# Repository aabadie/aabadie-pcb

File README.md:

aabadie-pcb board design and support
====================================

This repository contains both the Kicad project used to design aabadie-pcb board and also a RIOT port to this board.

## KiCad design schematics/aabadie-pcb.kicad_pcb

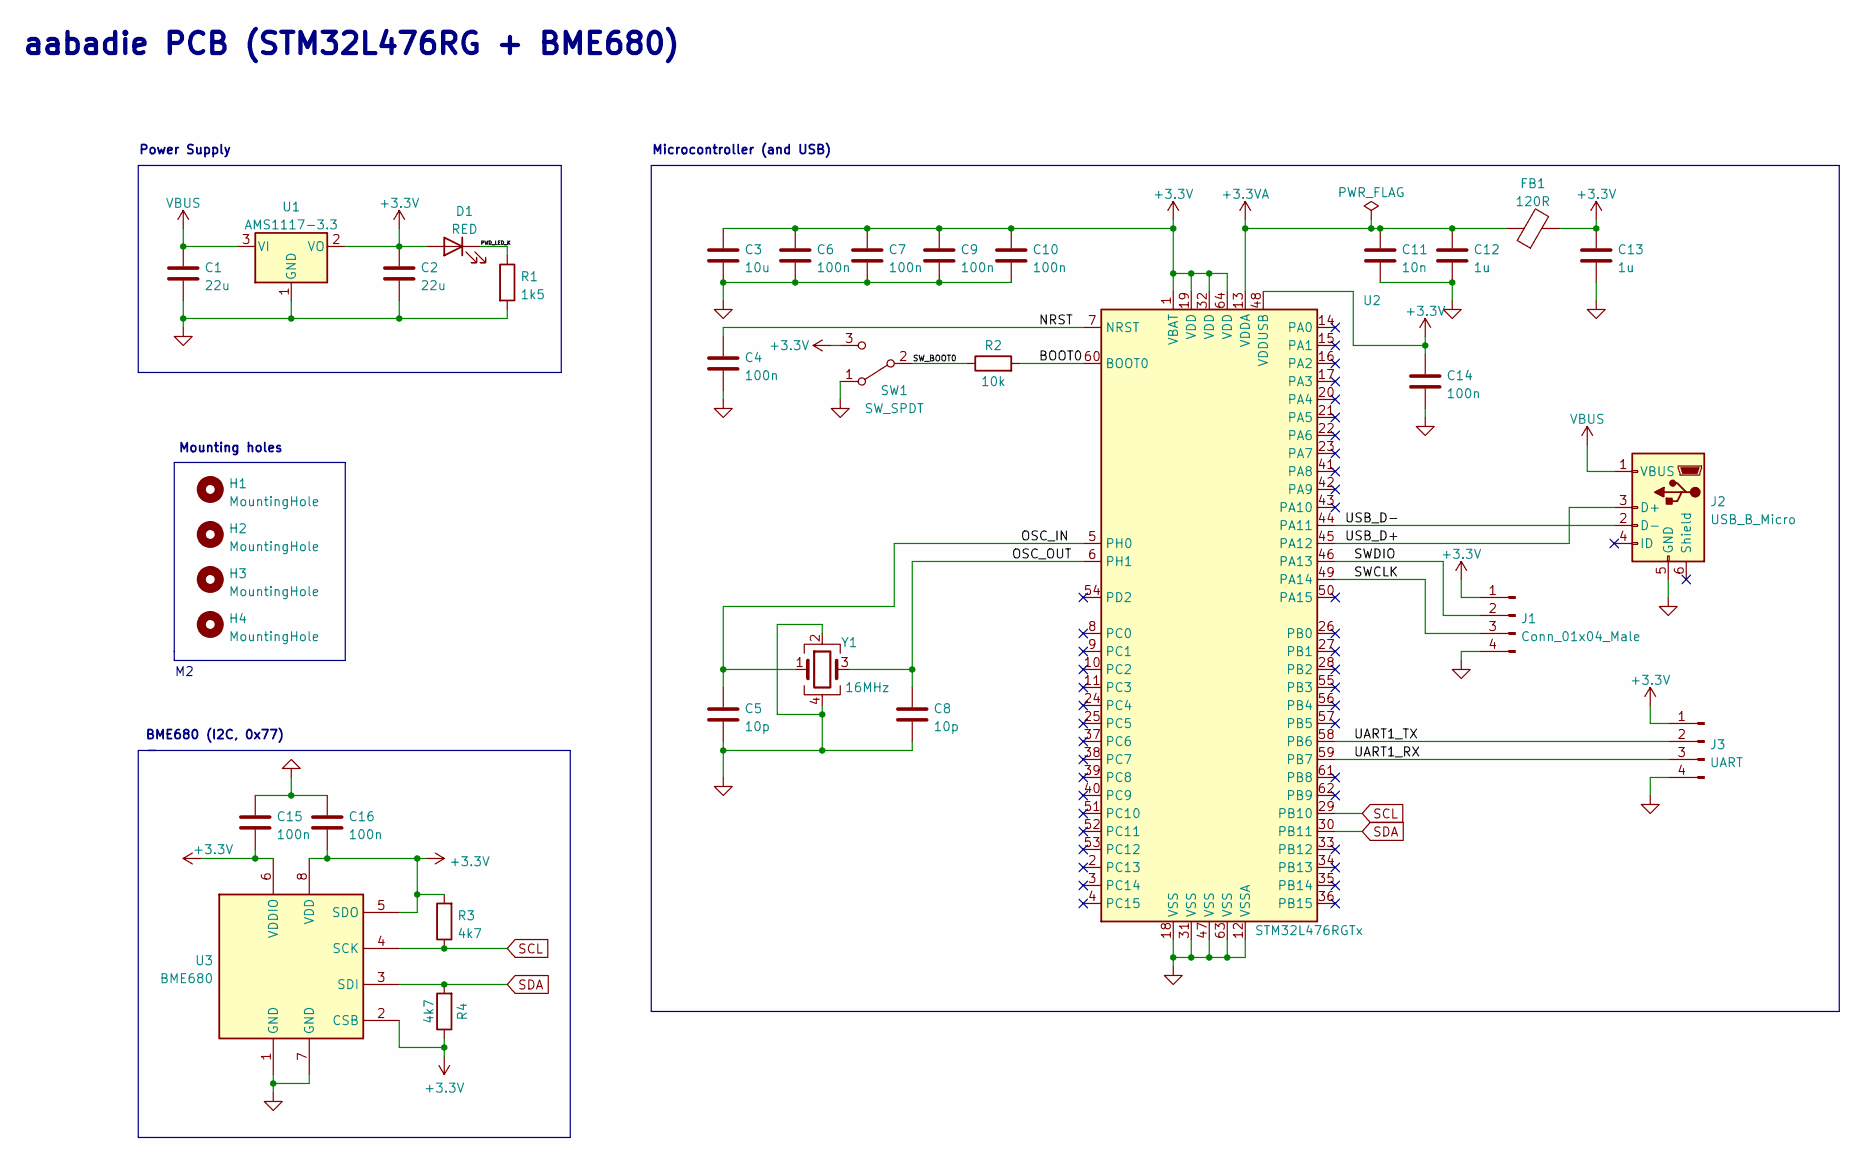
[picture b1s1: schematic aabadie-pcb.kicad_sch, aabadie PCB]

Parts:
C1, C2: 22u; C_0805_2012Metric
C3: 10u; C_0603_1608Metric
C4, C6, C7, C9, C10, C14, C15, C16: 100n; C_0402_1005Metric
C5, C8: 10p; C_0402_1005Metric
C11: 10n; C_0402_1005Metric
C12, C13: 1u; C_0402_1005Metric
D1: RED; LED_0402_1005Metric
FB1: 120R; L_0402_1005Metric
H1, H2, H3, H4: MountingHole; MountingHole_2.2mm_M2
J1: Conn_01x04_Male; PinHeader_1x04_P2.54mm_Vertical
J2: USB_B_Micro; USB_Micro-B_Wuerth_629105150521
J3: UART; PinHeader_1x04_P2.54mm_Vertical
R1: 1k5; R_0402_1005Metric
R2: 10k; R_0402_1005Metric
R3, R4: 4k7; R_0402_1005Metric
SW1: SW_SPDT; SW_SPDT_PCM12
U1: AMS1117-3.3; SOT-223-3_TabPin2
U2: STM32L476RGTx; LQFP-64_10x10mm_P0.5mm
U3: BME680; Bosch_LGA-8_3x3mm_P0.8mm_ClockwisePinNumbering
Y1: 16MHz; Crystal_SMD_3225-4Pin_3.2x2.5mm

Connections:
+3.3V: C2.2, C3.1, C6.1, C7.1, C9.1, C10.1, C13.1, C14.1, C15.2, C16.2, D1.2 (A), FB1.2, J1.1, J3.1, R3.2, R4.1, SW1.3 (C), U1.2 (VO), U2.1 (VBAT), U2.19 (VDD), U2.32 (VDD), U2.48 (VDDUSB), U2.64 (VDD), U3.2 (CSB), U3.5 (SDO), U3.6 (VDDIO), U3.8 (VDD)
+3.3VA: C11.1, C12.1, FB1.1, U2.13 (VDDA)
/BOOT0: R2.2, U2.60 (BOOT0)
/NRST: C4.1, U2.7 (NRST)
/OSC_IN: C5.1, U2.5 (PH0), Y1.1
/OSC_OUT: C8.1, U2.6 (PH1), Y1.3
/PWD_LED_K: D1.1 (K), R1.1
/SWCLK: J1.3, U2.49 (PA14)
/SWDIO: J1.2, U2.46 (PA13)
/SW_BOOT0: R2.1, SW1.2 (B)
/UART1_RX: J3.3, U2.59 (PB7)
/UART1_TX: J3.2, U2.58 (PB6)
/USB_D+: J2.3 (D+), U2.45 (PA12)
/USB_D-: J2.2 (D-), U2.44 (PA11)
GND: C1.2, C2.1, C3.2, C4.2, C5.2, C6.2, C7.2, C8.2, C9.2, C10.2, C11.2, C12.2, C13.2, C14.2, C15.1, C16.1, J1.4, J2.5 (GND), J3.4, R1.2, SW1.1 (A), U1.1 (GND), U2.12 (VSSA), U2.18 (VSS), U2.31 (VSS), U2.47 (VSS), U2.63 (VSS), U3.1 (GND), U3.7 (GND), Y1.2, Y1.4
SCL: R3.1, U2.29 (PB10), U3.4 (SCK)
SDA: R4.2, U2.30 (PB11), U3.3 (SDI)
VBUS: C1.1, J2.1 (VBUS), U1.3 (VI)

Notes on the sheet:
aabadie PCB (STM32L476RG + BME680)
Power Supply
BME680 (I2C, 0x77)
Mounting holes
Microcontroller (and USB)

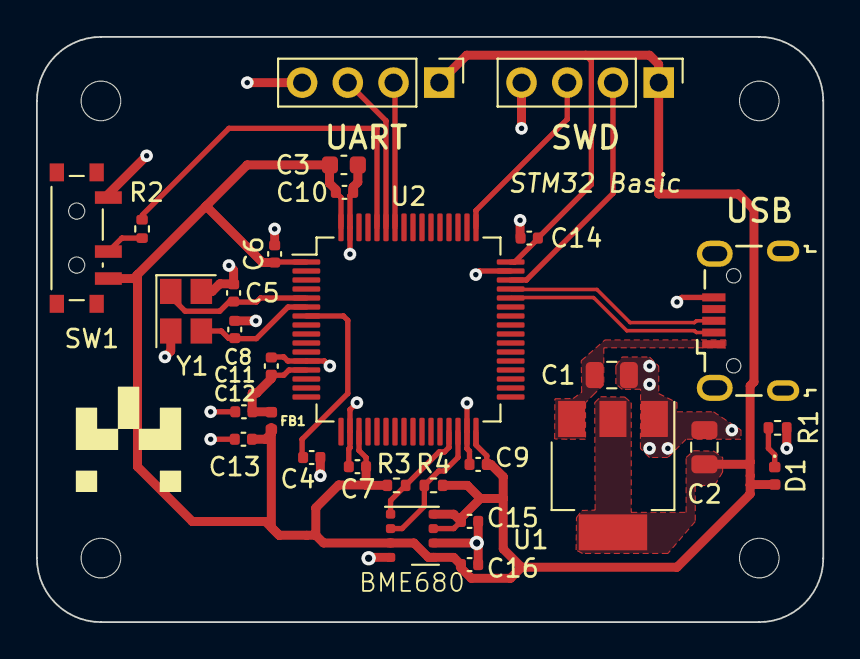
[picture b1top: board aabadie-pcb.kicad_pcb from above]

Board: 2 copper layers, 43.7 x 32.5 mm, 34 parts (0 on the bottom side), 18 nets.

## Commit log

2023-03-06 README.md: add README with basic notes and a picture of the board
2023-03-06 schematics: add initial version of Kicad project
2023-03-06 riot-bsp: add initial version of RIOT bsp
2023-03-06 assets: rotate board picture
2023-03-07 riot-bsp: add notes on how to compile, flash, access to stdio
2023-03-07 README.md: fix typo in board name and adjust setup notes
